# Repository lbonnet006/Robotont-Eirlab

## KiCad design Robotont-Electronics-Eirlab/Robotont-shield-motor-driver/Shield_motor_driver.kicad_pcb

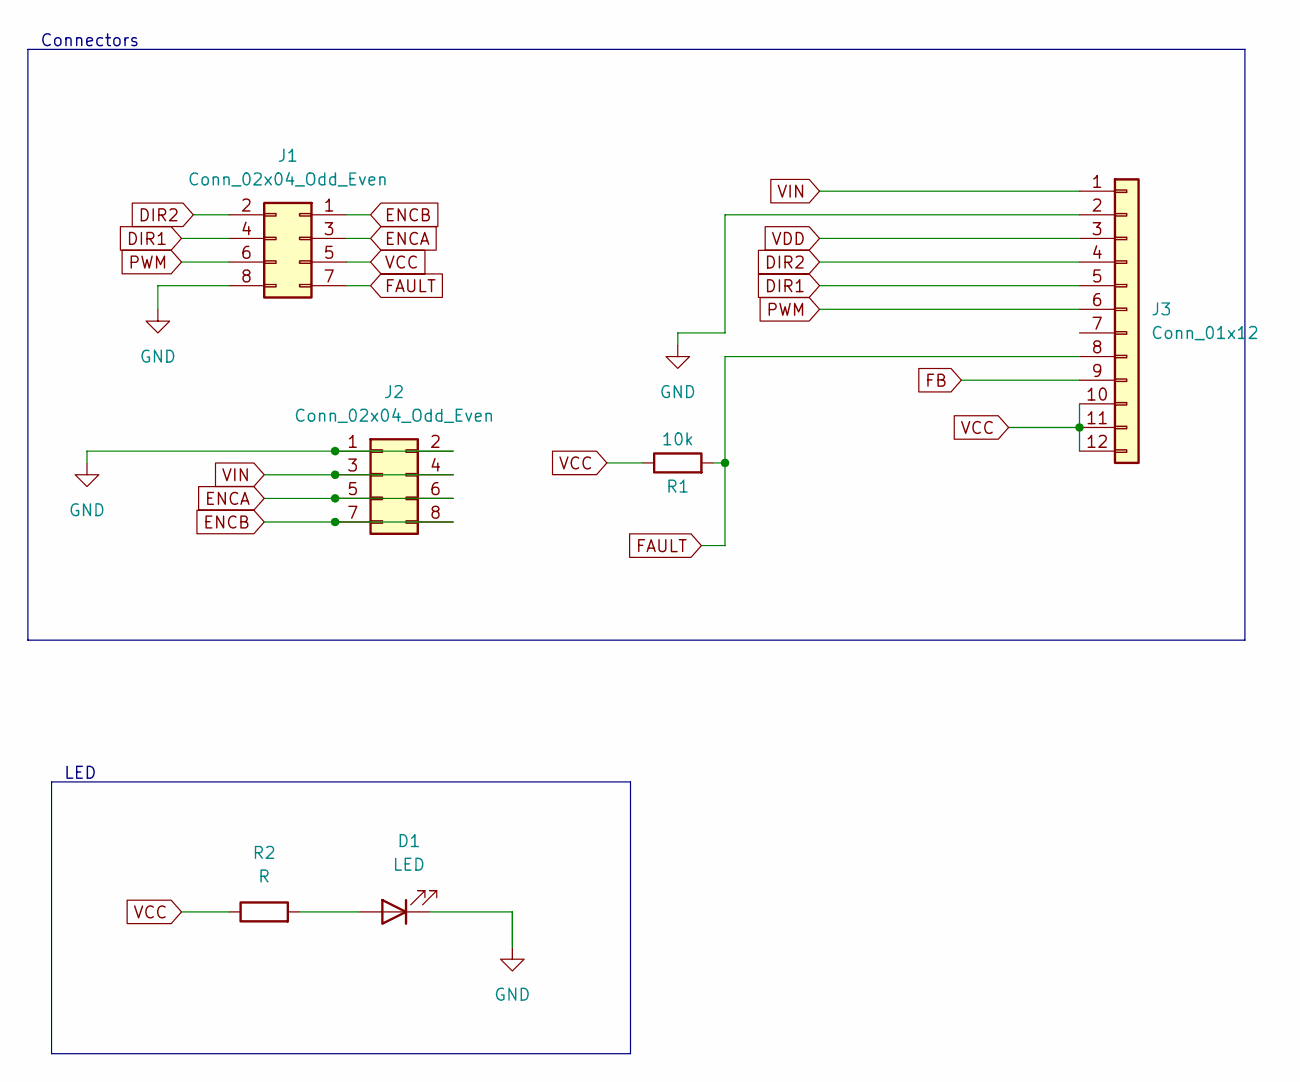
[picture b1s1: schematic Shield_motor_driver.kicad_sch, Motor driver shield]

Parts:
D1: LED; R_0805_2012Metric_Pad1.20x1.40mm_HandSolder
J1, J2: Conn_02x04_Odd_Even; PinHeader_2x04_P2.54mm_Vertical
J3: Conn_01x12; PinSocket_1x12_P2.54mm_Vertical
R1: 10k; R_0805_2012Metric_Pad1.20x1.40mm_HandSolder
R2: R; R_0805_2012Metric_Pad1.20x1.40mm_HandSolder

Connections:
DIR1: J1.4, J3.5
DIR2: J1.2, J3.4
ENCA: J1.3, J2.5, J2.6
ENCB: J1.1, J2.7, J2.8
FAULT: J1.7, J3.8, R1.2
FB: J3.9
GND: D1.1 (K), J1.8, J2.1, J2.2, J3.2
unnamed: D1.2 (A), R2.2
PWM: J1.6, J3.6
VCC: J1.5, J3.10, J3.11, J3.12, R1.1, R2.1
VDD: J3.3
VIN: J2.3, J2.4, J3.1

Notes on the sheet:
LED
Connectors

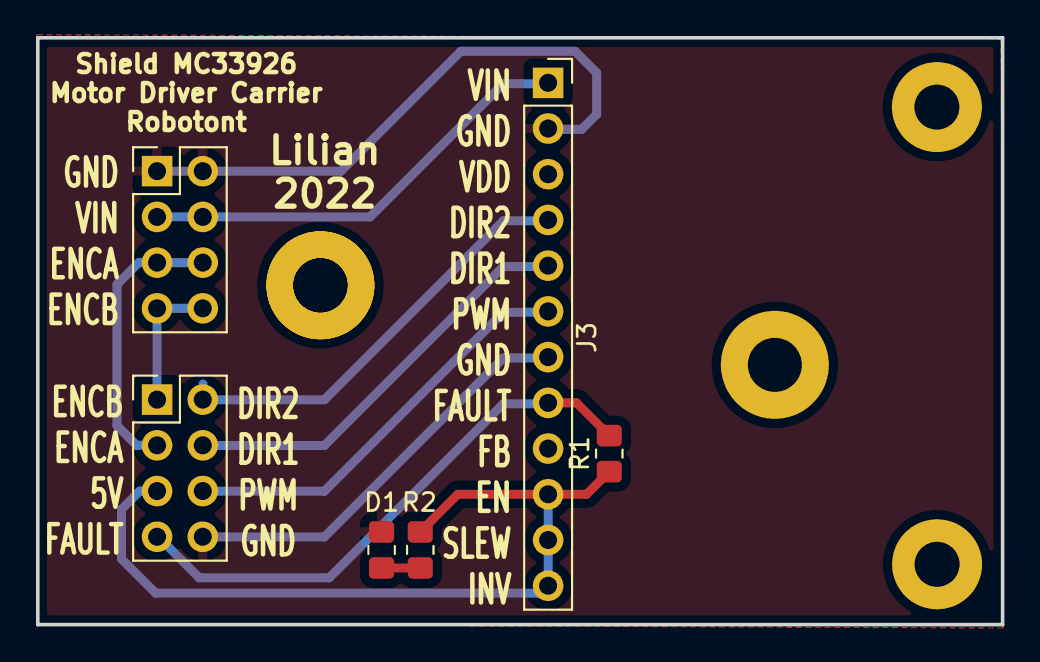
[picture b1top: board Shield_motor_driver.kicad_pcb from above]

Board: 2 copper layers, 53.6 x 32.6 mm, 10 parts (0 on the bottom side), 10 nets.

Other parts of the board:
H1, H2: MountingHole_Pad; MountingHole_3mm_Pad
H1#2, H2#2: MountingHole; MountingHole_2.5mm_Pad

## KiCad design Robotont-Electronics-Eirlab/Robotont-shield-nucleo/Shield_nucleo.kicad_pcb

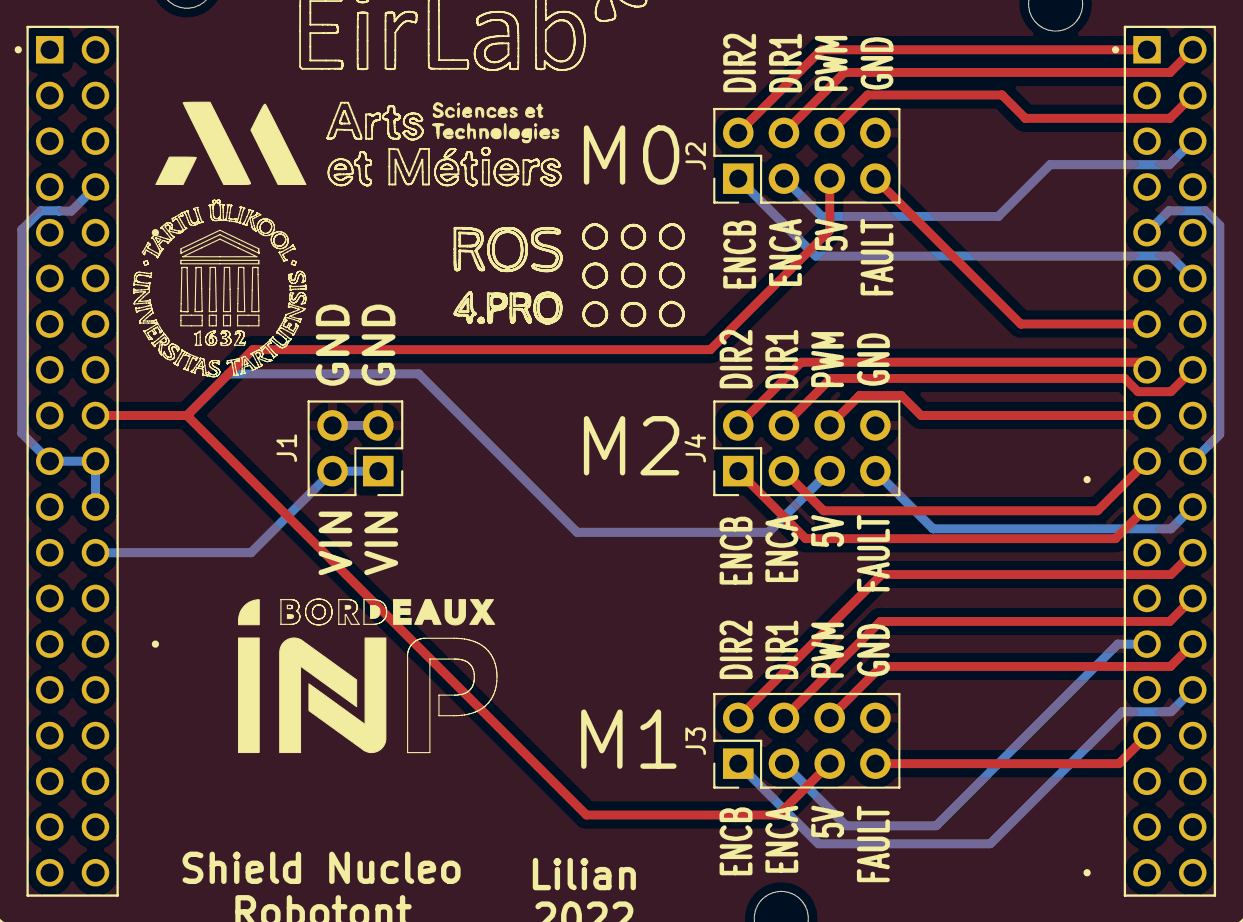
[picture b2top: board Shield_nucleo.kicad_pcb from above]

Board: 2 copper layers, 5 parts (0 on the bottom side), 23 nets.

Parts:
J1: Conn_02x02_Odd_Even; PinHeader_2x02_P2.54mm_Vertical
J2, J3, J4: Conn_02x04_Odd_Even; PinHeader_2x04_P2.54mm_Vertical
U1: NUCLEO-F446RE; MODULE_NUCLEO-F446RE

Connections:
5V: J2.5, J3.5, J4.5, U1.CN7_18 (CN7_+5V)
GND: J1.3, J1.4, J2.8, J3.8, J4.8
M1_DIR1: J2.4, U1.CN10_2 (PC8)
M1_DIR2: J2.2, U1.CN10_1 (PC9)
M1_ENCA: J2.3, U1.CN10_6 (PC5)
M1_ENCB: J2.1, U1.CN10_12 (PA12)
M1_FAULT: J2.7, U1.CN10_13 (PA6)
M1_PWM: J2.6, U1.CN10_4 (PC6)
M2_DIR1: J3.4, U1.CN10_26 (PB15)
M2_DIR2: J3.2, U1.CN10_24 (PB1)
M2_ENCA: J3.3, U1.CN10_27 (PB4)
M2_ENCB: J3.1, U1.CN10_30 (PB13)
M2_FAULT: J3.7, U1.CN10_31 (PB3)
M2_PWM: J3.6, U1.CN10_28 (PB14)
M3_DIR1: J4.4, U1.CN10_16 (PB12)
M3_DIR2: J4.2, U1.CN10_15 (PA7)
M3_ENCA: J4.3, U1.CN10_19 (PC7)
M3_ENCB: J4.1, U1.CN10_21 (PA9)
M3_FAULT: J4.7, U1.CN10_22 (PB2)
M3_PWM: J4.6, U1.CN10_17 (PB6)
unnamed: U1.CN7_8 (CN7_GND), U1.CN7_19 (CN7_GND), U1.CN7_20 (CN7_GND), U1.CN7_22 (CN7_GND)
unnamed: U1.CN10_9 (CN10_GND), U1.CN10_20 (CN10_GND)
VIN: J1.1, J1.2, U1.CN7_24 (CN7_VIN)

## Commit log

2022-06-29 electronics-3_mechanics-1
2022-06-29 electronics-4
2022-06-29 electronics-5
2022-07-11 mechanics_V3
2022-07-11 old_version
2022-07-11 Mechanics-V3.1
2022-07-11 3D-print
2022-07-21 Firmware_v2
2022-07-21 Firmware-v2
2022-07-21 final_update
2022-07-21 Electronics-6
